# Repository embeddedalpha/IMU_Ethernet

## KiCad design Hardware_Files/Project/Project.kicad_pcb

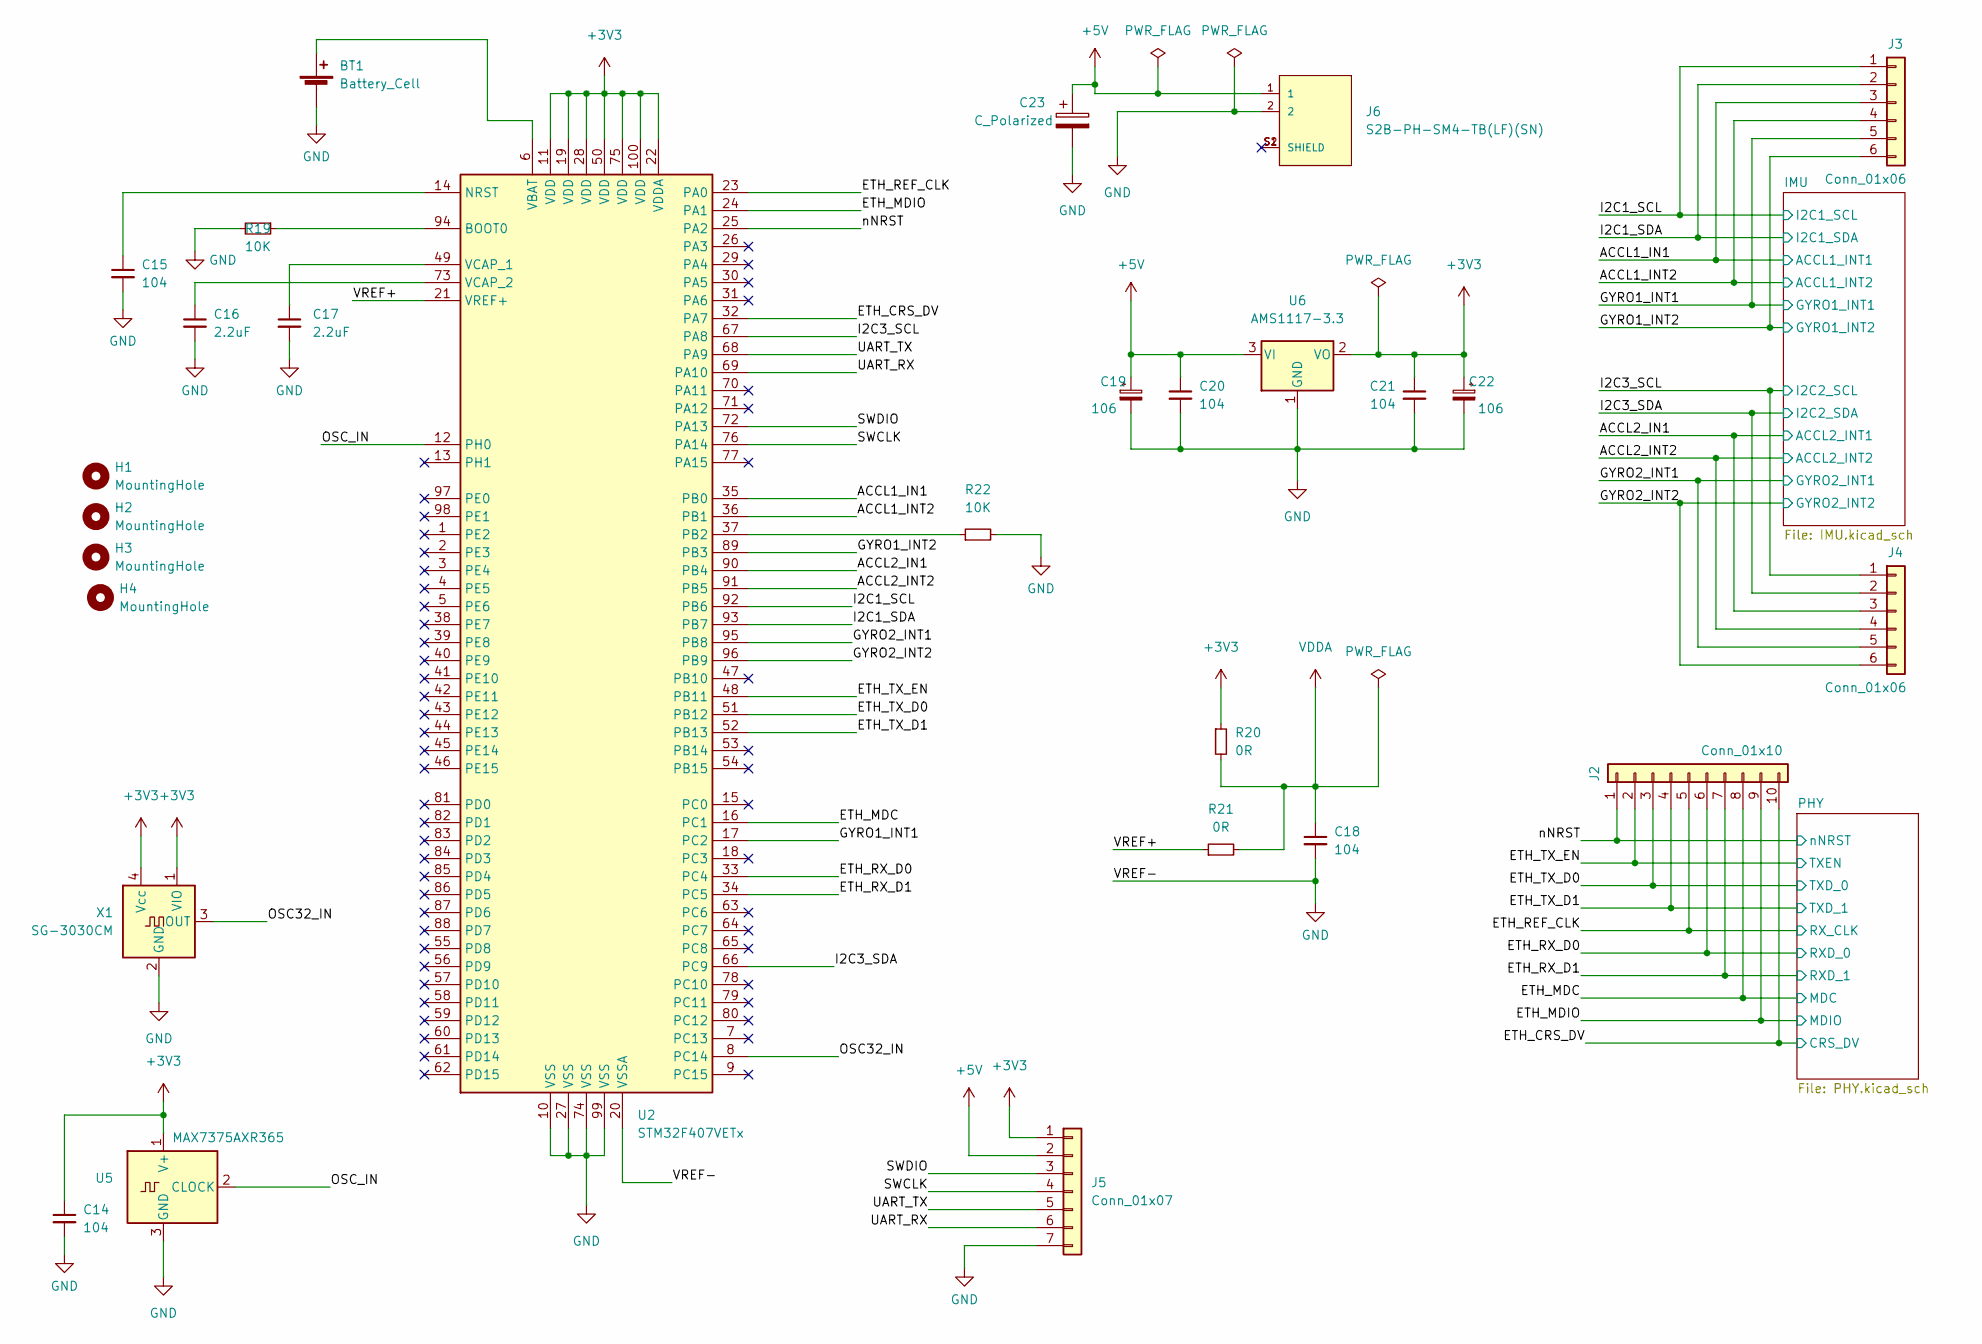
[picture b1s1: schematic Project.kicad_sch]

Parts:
BT1: Battery_Cell; BatteryHolder_Keystone_3000_1x12mm
C14, C15, C18, C20, C21: 104; C_0201_0603Metric_Pad0.64x0.40mm_HandSolder
C16, C17: 2.2uF; C_0201_0603Metric_Pad0.64x0.40mm_HandSolder
C19, C22: 106; C_0201_0603Metric_Pad0.64x0.40mm_HandSolder
C23: C_Polarized; CP_Elec_4x4.5
H1, H2, H3, H4: MountingHole; MountingHole_2.2mm_M2_Pad_Via
J2: Conn_01x10; PinHeader_1x10_P1.00mm_Vertical_SMD_Pin1Right
J3, J4: Conn_01x06; PinHeader_1x06_P1.00mm_Vertical_SMD_Pin1Left
J5: Conn_01x07; PinHeader_1x07_P1.00mm_Vertical_SMD_Pin1Left
J6: S2B-PH-SM4-TB(LF)(SN); JST_S2B-PH-SM4-TB(LF)(SN)
R19, R22: 10K; R_0201_0603Metric_Pad0.64x0.40mm_HandSolder
R20, R21: 0R; R_0201_0603Metric_Pad0.64x0.40mm_HandSolder
U2: STM32F407VETx; LQFP-100_14x14mm_P0.5mm
U5: MAX7375AXR365; SOT-323_SC-70
U6: AMS1117-3.3; SOT-223-3_TabPin2
X1: SG-3030CM; Oscillator_SMD_SeikoEpson_SG3030CM

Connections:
+5V: C19.1, C20.1, C23.1, J5.2, J6.1, U6.3 (VI)
/ACCL1_IN1: J3.3, U2.35 (PB0); also elsewhere on the board
/ACCL1_INT2: J3.4, U2.36 (PB1); also elsewhere on the board
/ACCL2_IN1: J4.3, U2.90 (PB4); also elsewhere on the board
/ACCL2_INT2: J4.4, U2.91 (PB5); also elsewhere on the board
/ETH_CRS_DV: J2.10, U2.32 (PA7); also elsewhere on the board
/ETH_MDC: J2.8, U2.16 (PC1); also elsewhere on the board
/ETH_MDIO: J2.9, U2.24 (PA1); also elsewhere on the board
/ETH_REF_CLK: J2.5, U2.23 (PA0); also elsewhere on the board
/ETH_RX_D0: J2.6, U2.33 (PC4); also elsewhere on the board
/ETH_RX_D1: J2.7, U2.34 (PC5); also elsewhere on the board
/ETH_TX_D0: J2.3, U2.51 (PB12); also elsewhere on the board
/ETH_TX_D1: J2.4, U2.52 (PB13); also elsewhere on the board
/ETH_TX_EN: J2.2, U2.48 (PB11); also elsewhere on the board
/GYRO1_INT1: J3.5, U2.17 (PC2); also elsewhere on the board
/GYRO1_INT2: J3.6, U2.89 (PB3); also elsewhere on the board
/GYRO2_INT1: J4.5, U2.95 (PB8); also elsewhere on the board
/GYRO2_INT2: J4.6, U2.96 (PB9); also elsewhere on the board
/I2C1_SCL: J3.1, U2.92 (PB6); also elsewhere on the board
/I2C1_SDA: J3.2, U2.93 (PB7); also elsewhere on the board
/I2C3_SCL: J4.1, U2.67 (PA8); also elsewhere on the board
/I2C3_SDA: J4.2, U2.66 (PC9); also elsewhere on the board
/OSC32_IN: U2.8 (PC14), X1.3 (OUT)
/OSC_IN: U2.12 (PH0), U5.2 (CLOCK)
/SWCLK: J5.4, U2.76 (PA14)
/SWDIO: J5.3, U2.72 (PA13)
/UART_RX: J5.6, U2.69 (PA10)
/UART_TX: J5.5, U2.68 (PA9)
/VREF+: R21.1, U2.21 (VREF+)
/nNRST: J2.1, U2.25 (PA2); also elsewhere on the board
GND: BT1.2 (-), C14.2, C15.2, C16.2, C17.2, C18.2, C19.2, C20.2, C21.2, C22.2, C23.2, J5.7, J6.2, R19.2, R22.2, U2.10 (VSS), U2.20 (VSSA), U2.27 (VSS), U2.74 (VSS), U2.99 (VSS), U5.3 (GND), U6.1 (GND), X1.2 (GND); also elsewhere on the board
unnamed: BT1.1 (+), U2.6 (VBAT)
unnamed: C15.1, U2.14 (NRST)
unnamed: R22.1, U2.37 (PB2)
unnamed: C17.1, U2.49 (VCAP_1)
unnamed: C16.1, U2.73 (VCAP_2)
unnamed: R19.1, U2.94 (BOOT0)
VCC: C14.1, C21.1, C22.1, J5.1, R20.1, U2.11 (VDD), U2.19 (VDD), U2.22 (VDDA), U2.28 (VDD), U2.50 (VDD), U2.75 (VDD), U2.100 (VDD), U5.1 (V+), U6.2 (VO), X1.1 (VIO), X1.4 (Vcc); also elsewhere on the board
VDDA: C18.1, R20.2, R21.2; also elsewhere on the board

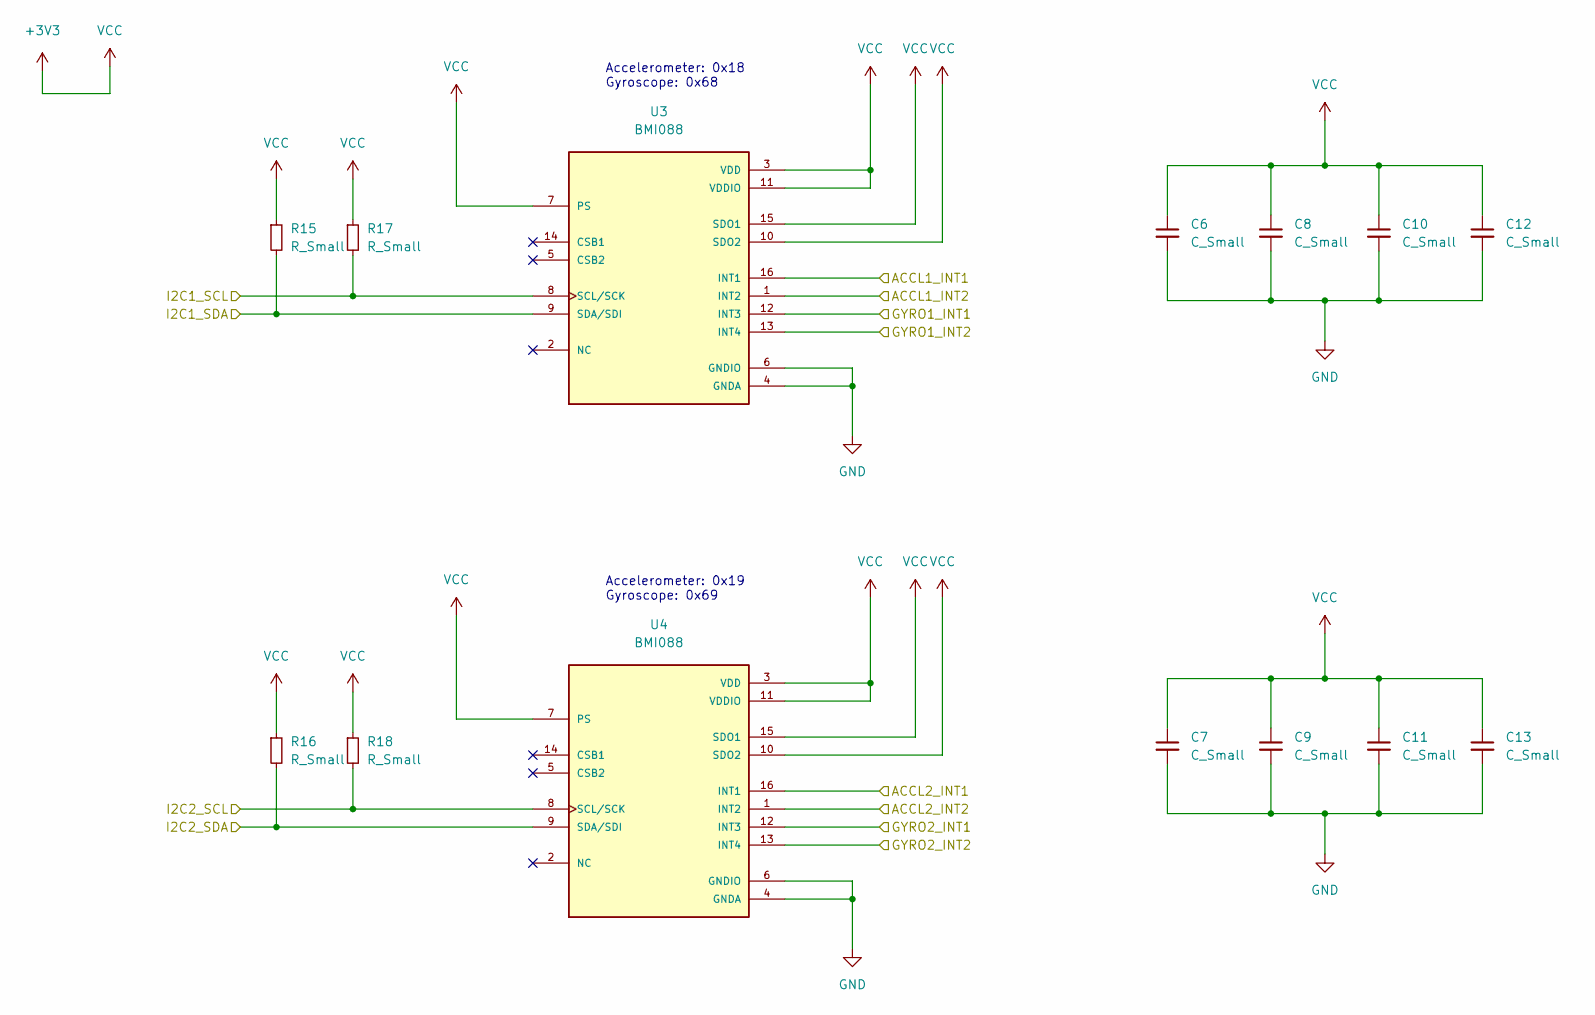
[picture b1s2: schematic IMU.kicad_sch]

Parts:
C6, C7, C8, C9, C10, C11, C12, C13: C_Small; C_0201_0603Metric_Pad0.64x0.40mm_HandSolder
R15, R16, R17, R18: R_Small; R_0201_0603Metric_Pad0.64x0.40mm_HandSolder
U3, U4: BMI088; PQFN50P450X300X100-16N

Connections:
/ACCL1_IN1: U3.16 (INT1); also elsewhere on the board
/ACCL1_INT2: U3.1 (INT2); also elsewhere on the board
/ACCL2_IN1: U4.16 (INT1); also elsewhere on the board
/ACCL2_INT2: U4.1 (INT2); also elsewhere on the board
/GYRO1_INT1: U3.12 (INT3); also elsewhere on the board
/GYRO1_INT2: U3.13 (INT4); also elsewhere on the board
/GYRO2_INT1: U4.12 (INT3); also elsewhere on the board
/GYRO2_INT2: U4.13 (INT4); also elsewhere on the board
/I2C1_SCL: R17.2, U3.8 (SCL/SCK); also elsewhere on the board
/I2C1_SDA: R15.2, U3.9 (SDA/SDI); also elsewhere on the board
/I2C3_SCL: R18.2, U4.8 (SCL/SCK); also elsewhere on the board
/I2C3_SDA: R16.2, U4.9 (SDA/SDI); also elsewhere on the board
GND: C6.2, C7.2, C8.2, C9.2, C10.2, C11.2, C12.2, C13.2, U3.4 (GNDA), U3.6 (GNDIO), U4.4 (GNDA), U4.6 (GNDIO); also elsewhere on the board
VCC: C6.1, C7.1, C8.1, C9.1, C10.1, C11.1, C12.1, C13.1, R15.1, R16.1, R17.1, R18.1, U3.3 (VDD), U3.7 (PS), U3.10 (SDO2), U3.11 (VDDIO), U3.15 (SDO1), U4.3 (VDD), U4.7 (PS), U4.10 (SDO2), U4.11 (VDDIO), U4.15 (SDO1); also elsewhere on the board

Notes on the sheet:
Accelerometer: 0x18 Gyroscope: 0x68
Accelerometer: 0x19 Gyroscope: 0x69

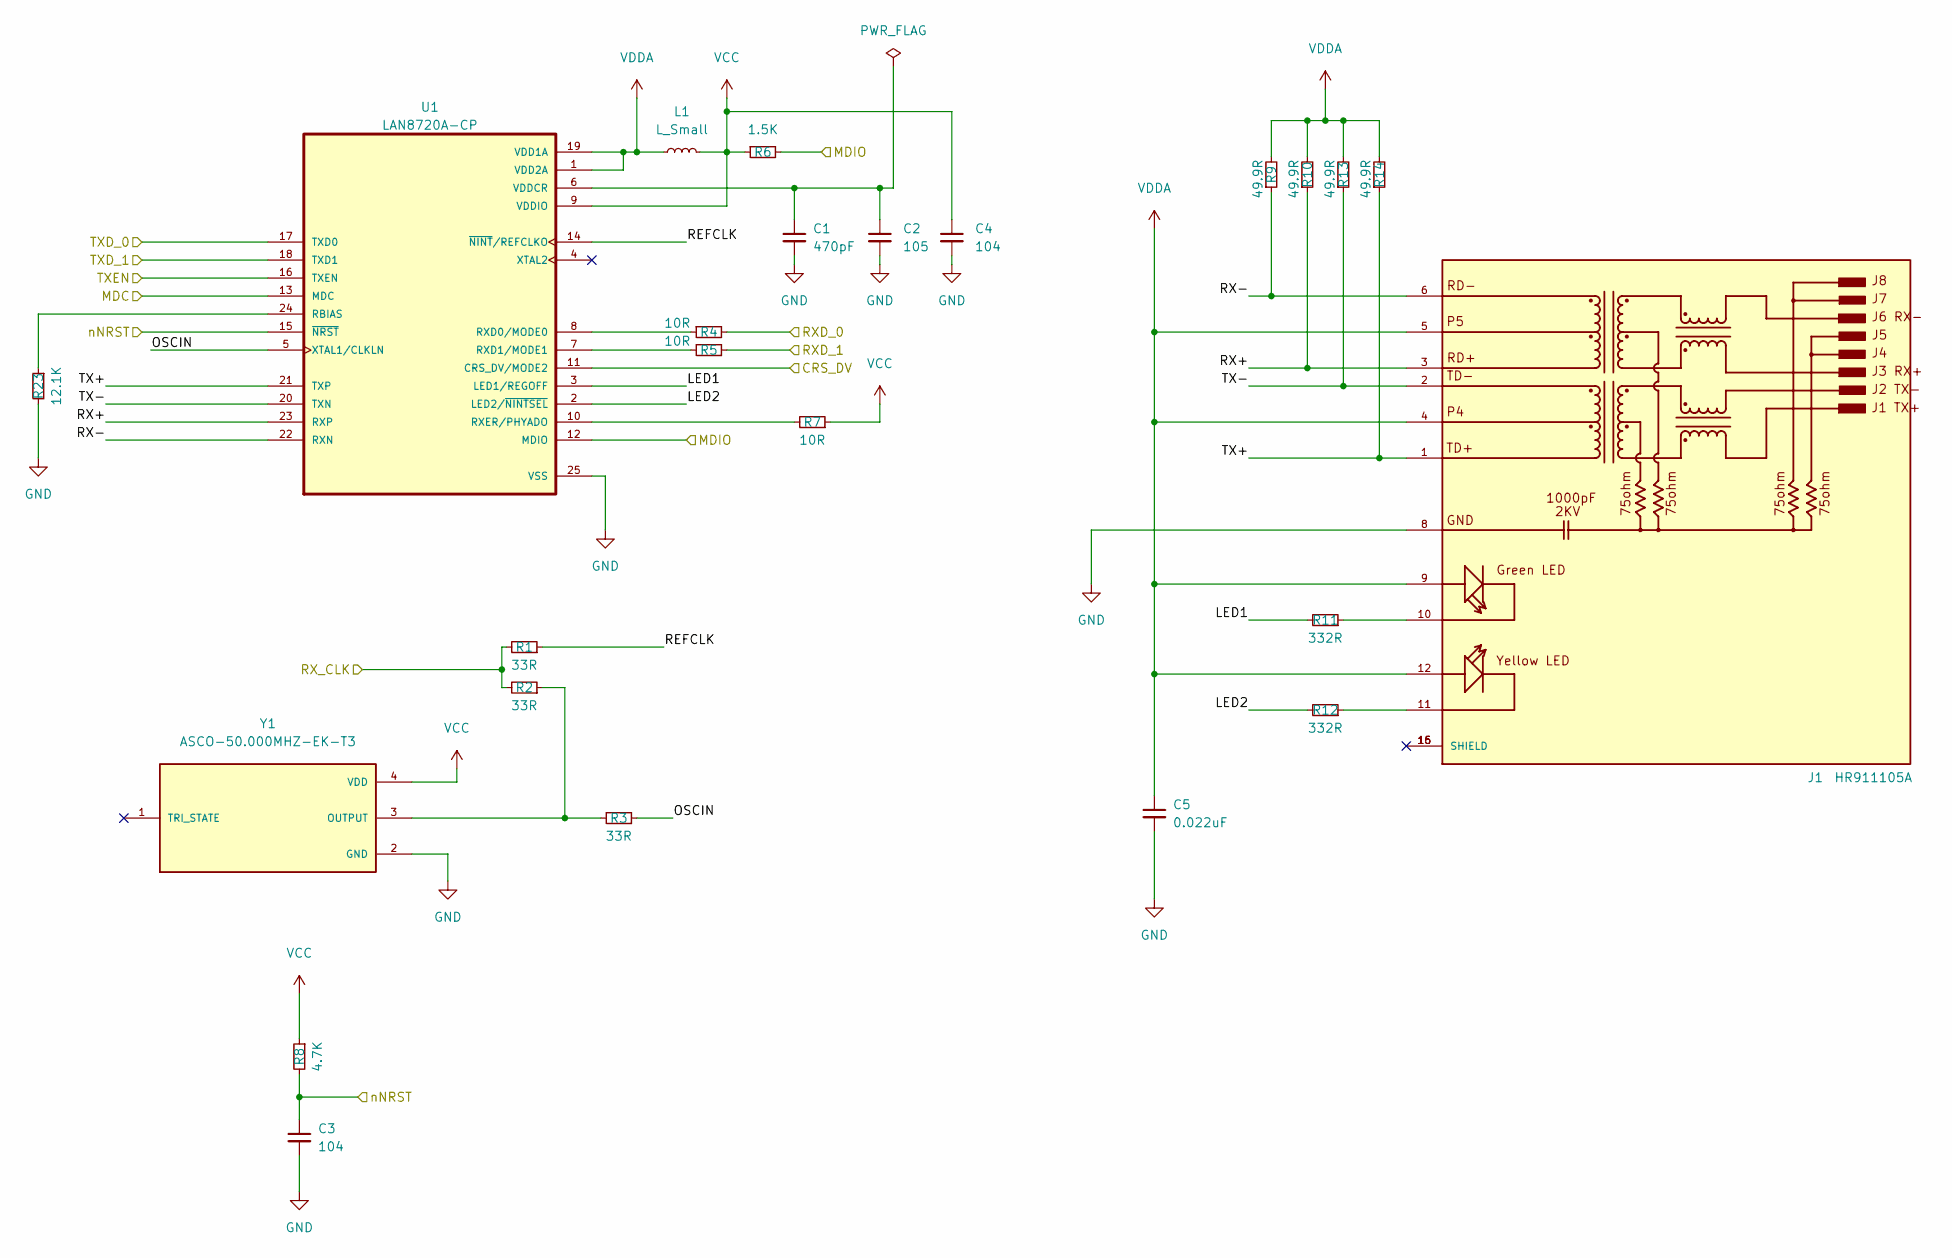
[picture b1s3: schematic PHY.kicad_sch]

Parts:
C1: 470pF; C_0201_0603Metric_Pad0.64x0.40mm_HandSolder
C2: 105; C_0201_0603Metric_Pad0.64x0.40mm_HandSolder
C3, C4: 104; C_0201_0603Metric_Pad0.64x0.40mm_HandSolder
C5: 0.022uF; C_0201_0603Metric_Pad0.64x0.40mm_HandSolder
J1: HR911105A; HANRUN_HR911105A; PARTREV A
L1: L_Small; L_0402_1005Metric_Pad0.77x0.64mm_HandSolder
R1, R2, R3: 33R; R_0201_0603Metric_Pad0.64x0.40mm_HandSolder
R4, R5, R7: 10R; R_0201_0603Metric_Pad0.64x0.40mm_HandSolder
R6: 1.5K; R_0201_0603Metric_Pad0.64x0.40mm_HandSolder
R8: 4.7K; R_0201_0603Metric_Pad0.64x0.40mm_HandSolder
R9, R10, R13, R14: 49.9R; R_0201_0603Metric_Pad0.64x0.40mm_HandSolder
R11, R12: 332R; R_0201_0603Metric_Pad0.64x0.40mm_HandSolder
R23: 12.1K; R_0201_0603Metric_Pad0.64x0.40mm_HandSolder
U1: LAN8720A-CP; QFN50P400X400X100-25N; PARTREV B
Y1: ASCO-50.000MHZ-EK-T3; XTAL_ASCO-50.000MHZ-EK-T3; PARTREV 10.12.2017

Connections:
/ETH_CRS_DV: U1.11 (CRS_DV/MODE2); also elsewhere on the board
/ETH_MDC: U1.13 (MDC); also elsewhere on the board
/ETH_MDIO: R6.2, U1.12 (MDIO); also elsewhere on the board
/ETH_REF_CLK: R1.2, R2.2; also elsewhere on the board
/ETH_RX_D0: R4.2; also elsewhere on the board
/ETH_RX_D1: R5.1; also elsewhere on the board
/ETH_TX_D0: U1.17 (TXD0); also elsewhere on the board
/ETH_TX_D1: U1.18 (TXD1); also elsewhere on the board
/ETH_TX_EN: U1.16 (TXEN); also elsewhere on the board
/PHY/LED1: R11.2, U1.3 (LED1/REGOFF)
/PHY/LED2: R12.2, U1.2 (LED2/~NINTSEL)
/PHY/OSCIN: R3.1, U1.5 (XTAL1/CLKLN)
/PHY/REFCLK: R1.1, U1.14 (~NINT/REFCLKO)
/PHY/RX+: J1.3, R10.1, U1.23 (RXP)
/PHY/RX-: J1.6, R9.1, U1.22 (RXN)
/PHY/TX+: J1.1, R14.1, U1.21 (TXP)
/PHY/TX-: J1.2, R13.1, U1.20 (TXN)
/nNRST: C3.1, R8.2, U1.15 (~NRST); also elsewhere on the board
GND: C1.2, C2.2, C3.2, C4.2, C5.2, J1.8, R23.2, U1.25 (VSS), Y1.2 (GND); also elsewhere on the board
unnamed: C1.1, C2.1, U1.6 (VDDCR)
unnamed: J1.10, R11.1
unnamed: J1.11, R12.1
unnamed: R2.1, R3.2, Y1.3 (OUTPUT)
unnamed: R4.1, U1.8 (RXD0/MODE0)
unnamed: R5.2, U1.7 (RXD1/MODE1)
unnamed: R7.2, U1.10 (RXER/PHYADO)
unnamed: R23.1, U1.24 (RBIAS)
VCC: C4.1, L1.2, R6.1, R7.1, R8.1, U1.9 (VDDIO), Y1.4 (VDD); also elsewhere on the board
VDDA: C5.1, J1.4, J1.5, J1.9, J1.12, L1.1, R9.2, R10.2, R13.2, R14.2, U1.1 (VDD2A), U1.19 (VDD1A); also elsewhere on the board

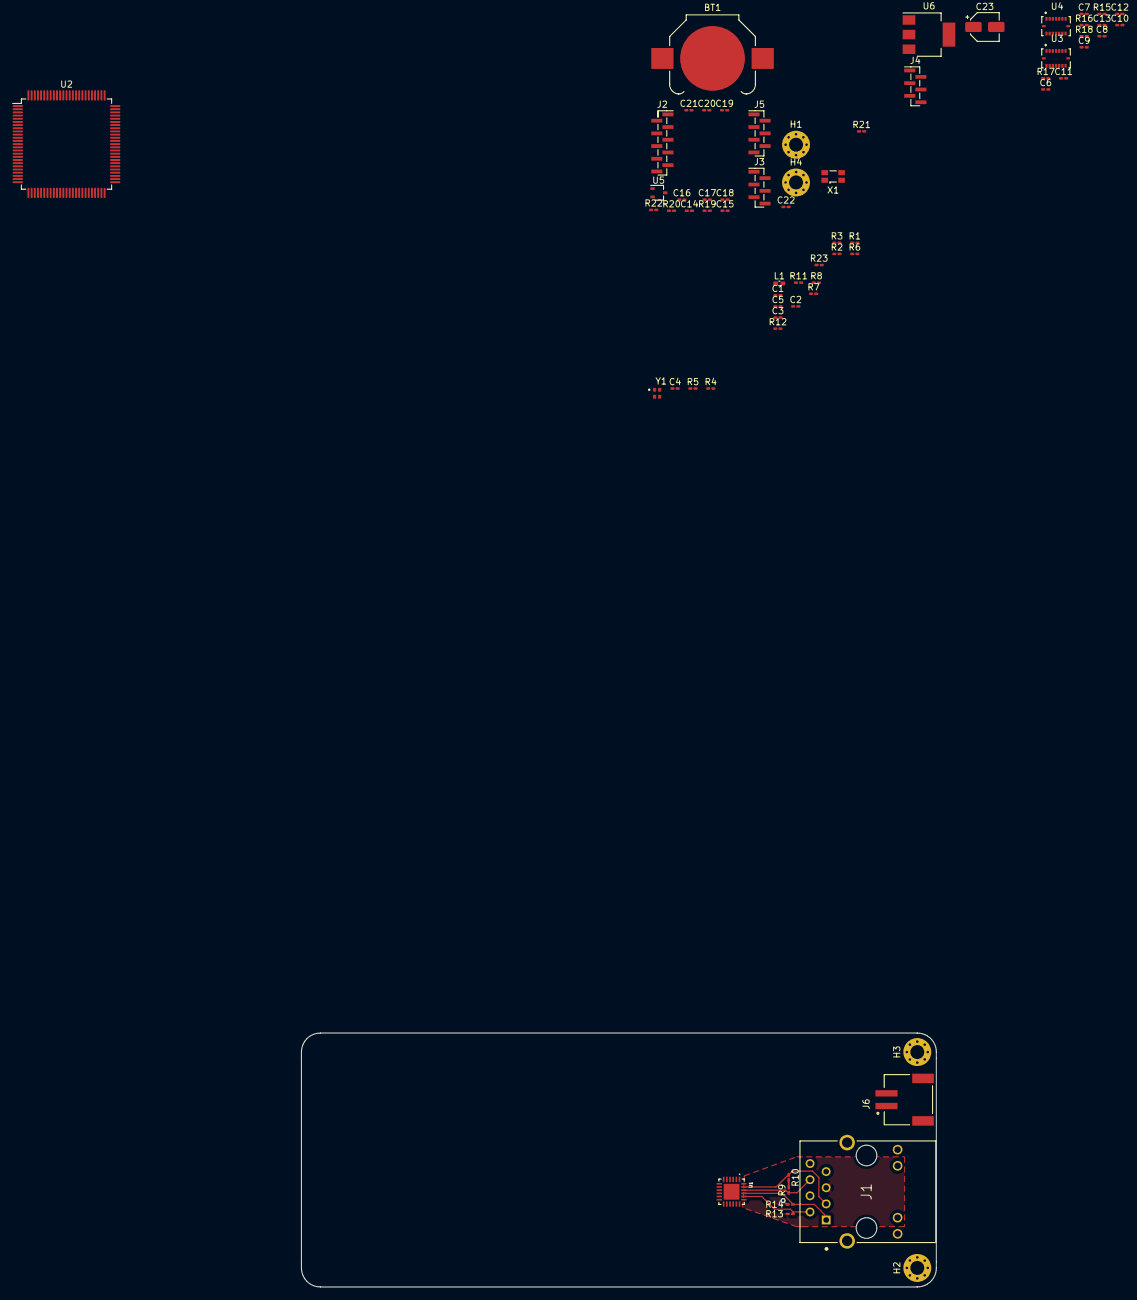
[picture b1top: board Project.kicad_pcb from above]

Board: 2 copper layers, 100.0 x 40.0 mm, 66 parts (0 on the bottom side), 55 nets.

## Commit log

2023-04-16 Repo Update
